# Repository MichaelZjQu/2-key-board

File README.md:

The two-key board is a 2 button macropad. It has 2 switches and 2 mini leds. It is powered by a xiao-rp2040.

Also there is a case:

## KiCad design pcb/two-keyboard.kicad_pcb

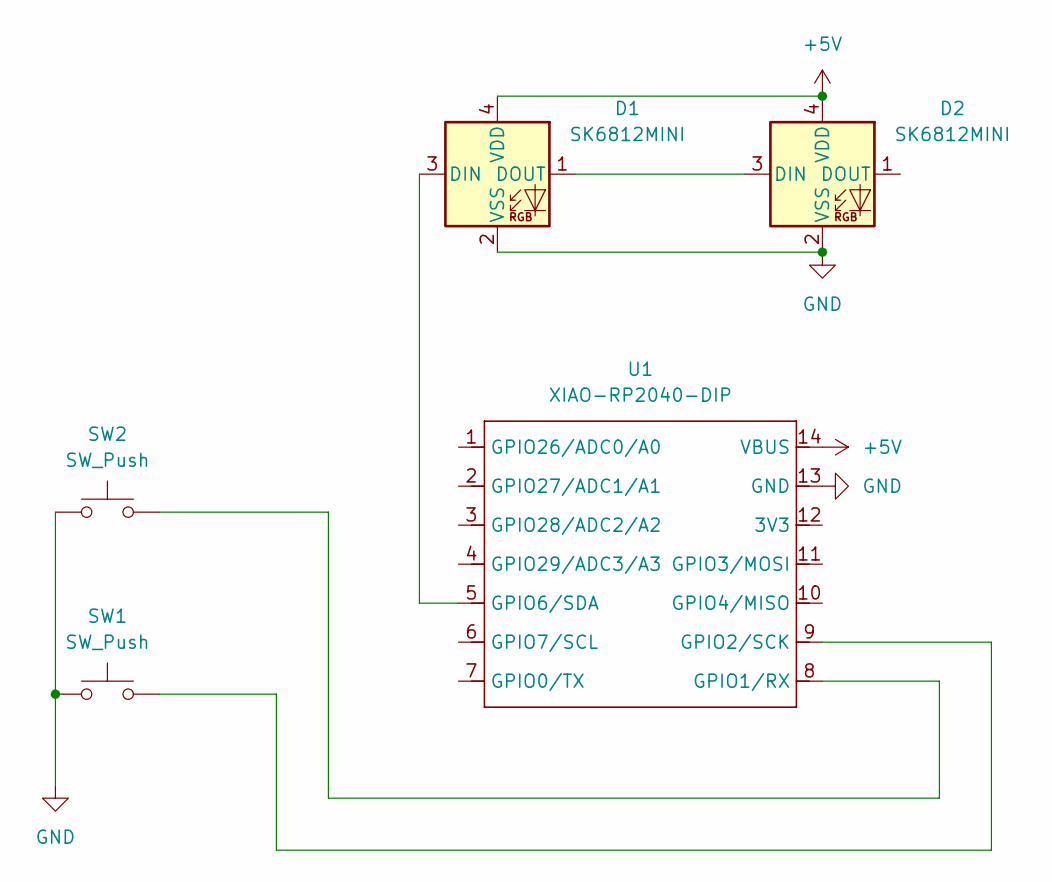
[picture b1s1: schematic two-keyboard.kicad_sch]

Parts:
D1, D2: SK6812MINI; LED_SK6812MINI_PLCC4_3.5x3.5mm_P1.75mm
SW1, SW2: SW_Push; SW_Cherry_MX_1.00u_PCB
U1: XIAO-RP2040-DIP

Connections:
+5V: D1.4 (VDD), D2.4 (VDD), U1.14 (VBUS)
GND: D1.2 (VSS), D2.2 (VSS), SW1.1, SW2.1, U1.13 (GND)
unnamed: D1.3 (DIN), U1.5 (GPIO6/SDA)
unnamed: D1.1 (DOUT), D2.3 (DIN)
unnamed: SW2.2, U1.8 (GPIO1/RX)
unnamed: SW1.2, U1.9 (GPIO2/SCK)

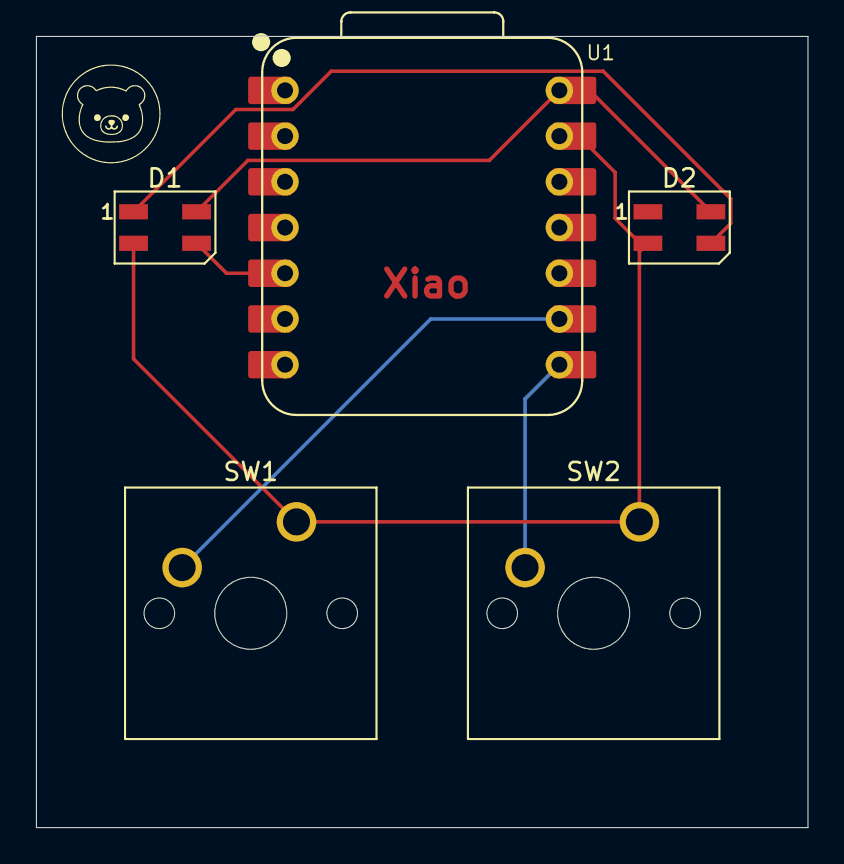
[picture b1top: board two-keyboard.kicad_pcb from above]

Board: 2 copper layers, 42.9 x 44.0 mm, 5 parts (0 on the bottom side), 6 nets.

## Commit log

2025-10-12 create imgs folder
2025-10-12 add imgs
2025-10-13 add ship reqs
2025-10-14 fix case holes
